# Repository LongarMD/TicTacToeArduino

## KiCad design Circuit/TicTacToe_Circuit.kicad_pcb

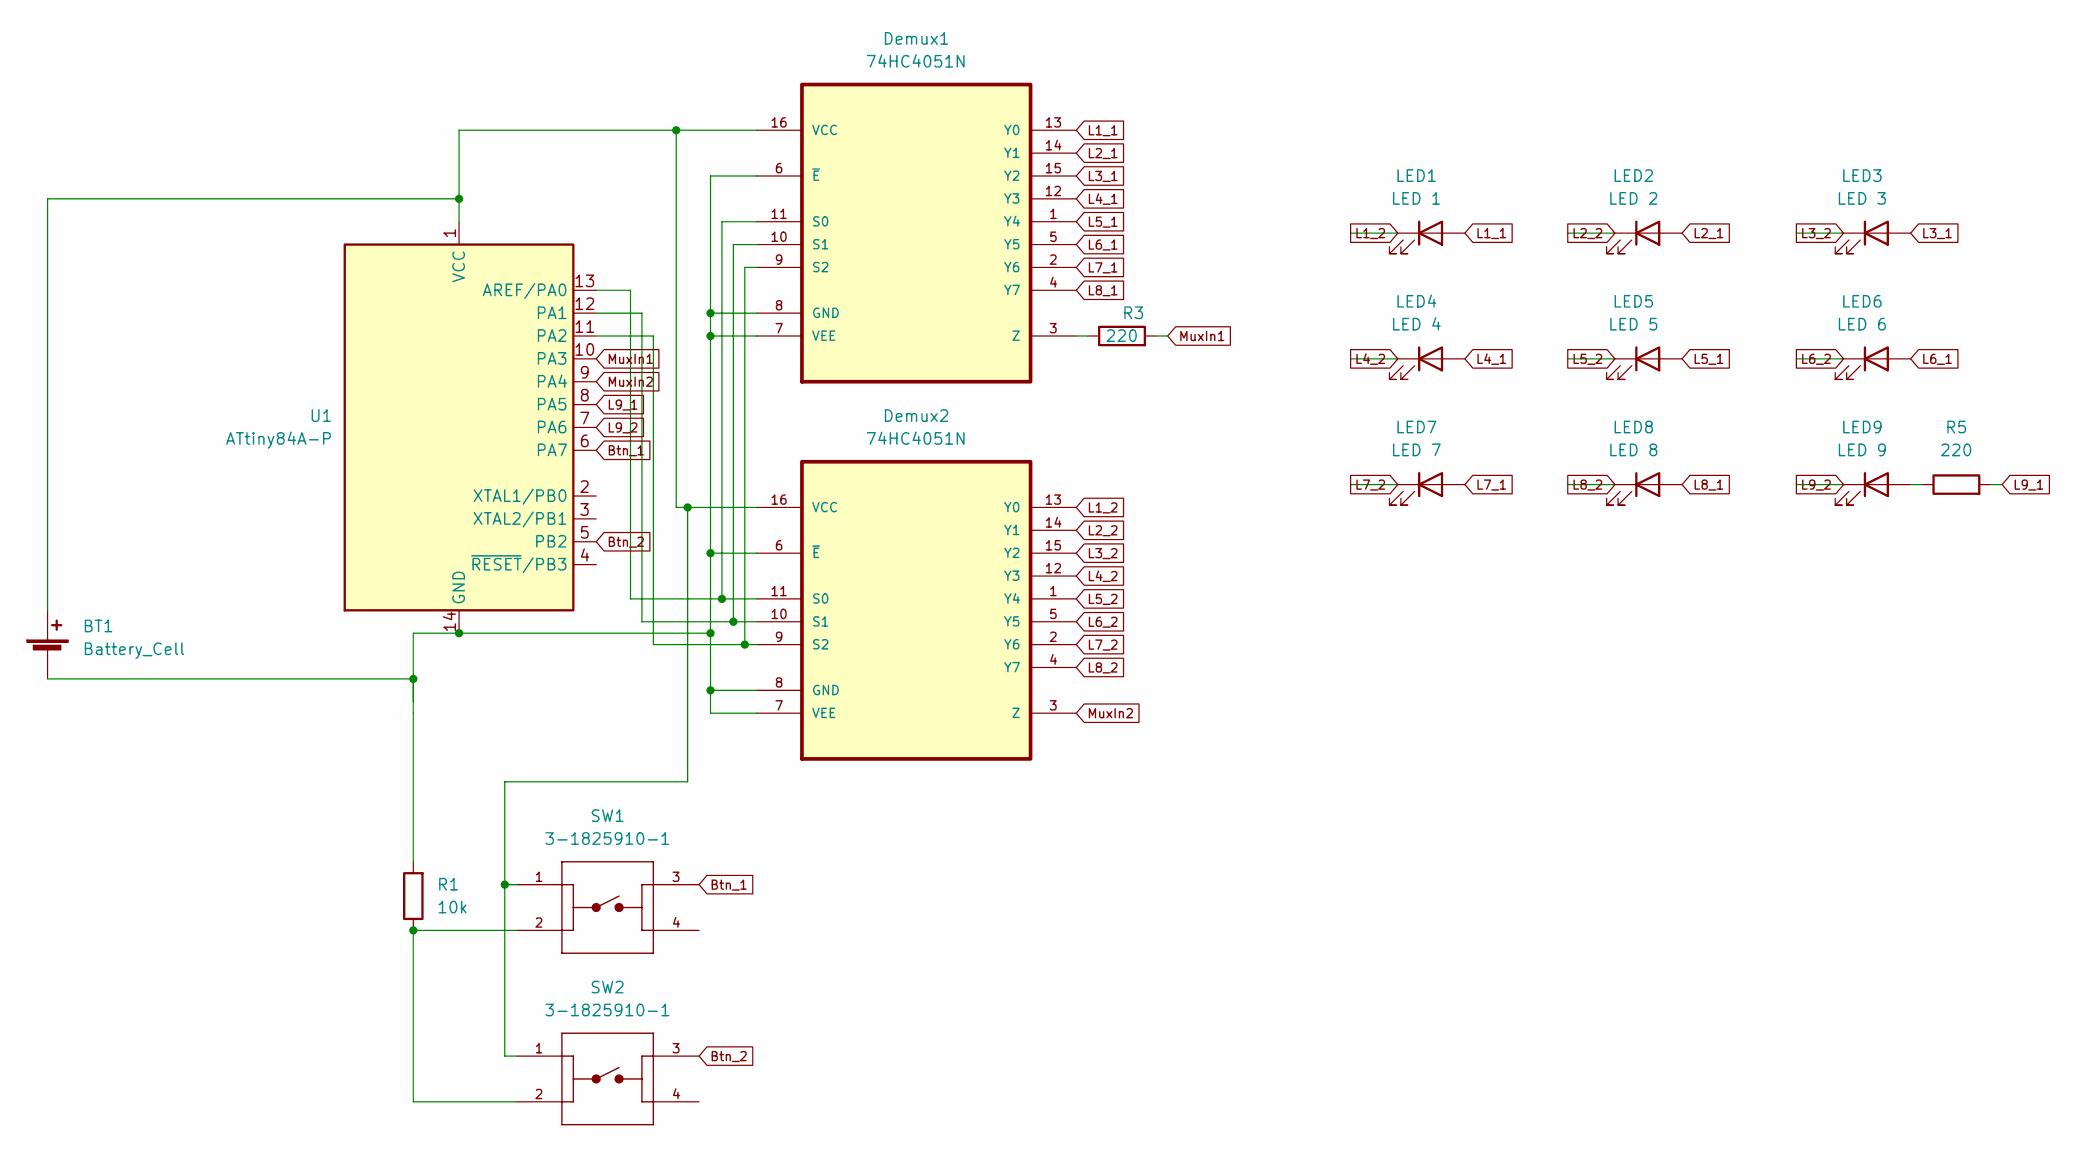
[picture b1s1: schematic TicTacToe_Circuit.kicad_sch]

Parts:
BT1: Battery_Cell; BatteryHolder_ComfortableElectronic_CH273-2450_1x2450
Demux1, Demux2: 74HC4051N; DIP254P762X420-16; MPN 74HC4051N
LED1: LED 1; LED_D5.0mm
LED2: LED 2; LED_D5.0mm
LED3: LED 3; LED_D5.0mm
LED4: LED 4; LED_D5.0mm
LED5: LED 5; LED_D5.0mm
LED6: LED 6; LED_D5.0mm
LED7: LED 7; LED_D5.0mm
LED8: LED 8; LED_D5.0mm
LED9: LED 9; LED_D5.0mm
R1: 10k; R_Axial_DIN0204_L3.6mm_D1.6mm_P7.62mm_Horizontal
R3, R5: 220; R_Axial_DIN0204_L3.6mm_D1.6mm_P7.62mm_Horizontal
SW1, SW2: 3-1825910-1; TE_3-1825910-1
U1: ATtiny84A-P; DIP-14_W7.62mm

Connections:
Btn_1: SW1.3, U1.6 (PA7)
Btn_2: SW2.3, U1.5 (PB2)
L1_1: Demux1.13 (Y0), LED1.2 (A)
L1_2: Demux2.13 (Y0), LED1.1 (K)
L2_1: Demux1.14 (Y1), LED2.2 (A)
L2_2: Demux2.14 (Y1), LED2.1 (K)
L3_1: Demux1.15 (Y2), LED3.2 (A)
L3_2: Demux2.15 (Y2), LED3.1 (K)
L4_1: Demux1.12 (Y3), LED4.2 (A)
L4_2: Demux2.12 (Y3), LED4.1 (K)
L5_1: Demux1.1 (Y4), LED5.2 (A)
L5_2: Demux2.1 (Y4), LED5.1 (K)
L6_1: Demux1.5 (Y5), LED6.2 (A)
L6_2: Demux2.5 (Y5), LED6.1 (K)
L7_1: Demux1.2 (Y6), LED7.2 (A)
L7_2: Demux2.2 (Y6), LED7.1 (K)
L8_1: Demux1.4 (Y7), LED8.2 (A)
L8_2: Demux2.4 (Y7), LED8.1 (K)
L9_1: R5.2, U1.8 (PA5)
L9_2: LED9.1 (K), U1.7 (PA6)
MuxIn1: R3.2, U1.10 (PA3)
MuxIn2: Demux2.3 (Z), U1.9 (PA4)
unnamed: Demux1.3 (Z), R3.1
unnamed: BT1.2 (-), Demux1.6 (~E), Demux1.7 (VEE), Demux1.8 (GND), Demux2.6 (~E), Demux2.7 (VEE), Demux2.8 (GND), R1.2, U1.14 (GND)
unnamed: Demux1.9 (S2), Demux2.9 (S2), U1.11 (PA2)
unnamed: Demux1.10 (S1), Demux2.10 (S1), U1.12 (PA1)
unnamed: Demux1.11 (S0), Demux2.11 (S0), U1.13 (AREF/PA0)
unnamed: BT1.1 (+), Demux1.16 (VCC), Demux2.16 (VCC), SW1.1, SW2.1, U1.1 (VCC)
unnamed: LED9.2 (A), R5.1
unnamed: R1.1, SW1.2, SW2.2

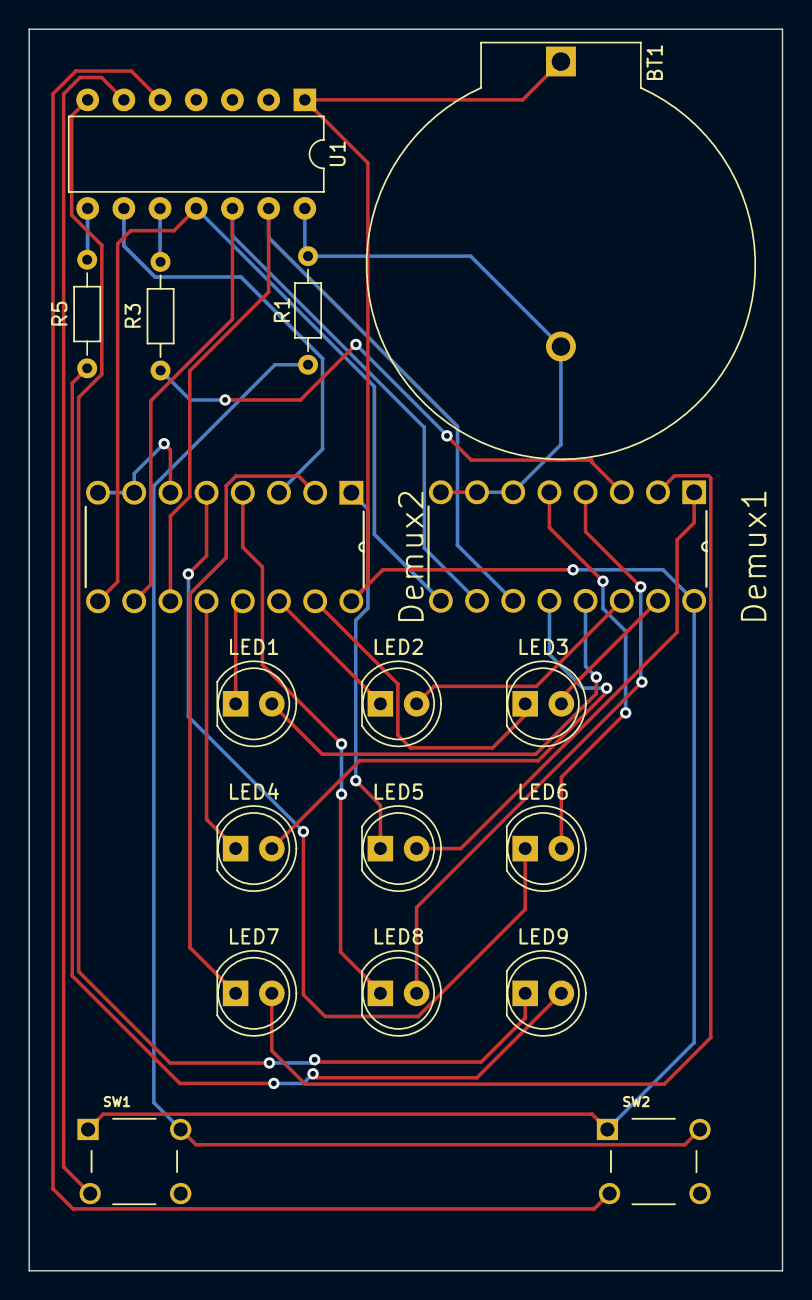
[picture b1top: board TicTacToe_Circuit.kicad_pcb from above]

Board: 2 copper layers, 52.9 x 87.1 mm, 18 parts (0 on the bottom side), 30 nets.

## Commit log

2022-02-26 init
2022-02-26 Blink, cursor
2022-02-26 Version 1.0A
2022-02-27 Adds basic end screen
2022-02-27 Attiny84 config
2022-02-27 Circuit
